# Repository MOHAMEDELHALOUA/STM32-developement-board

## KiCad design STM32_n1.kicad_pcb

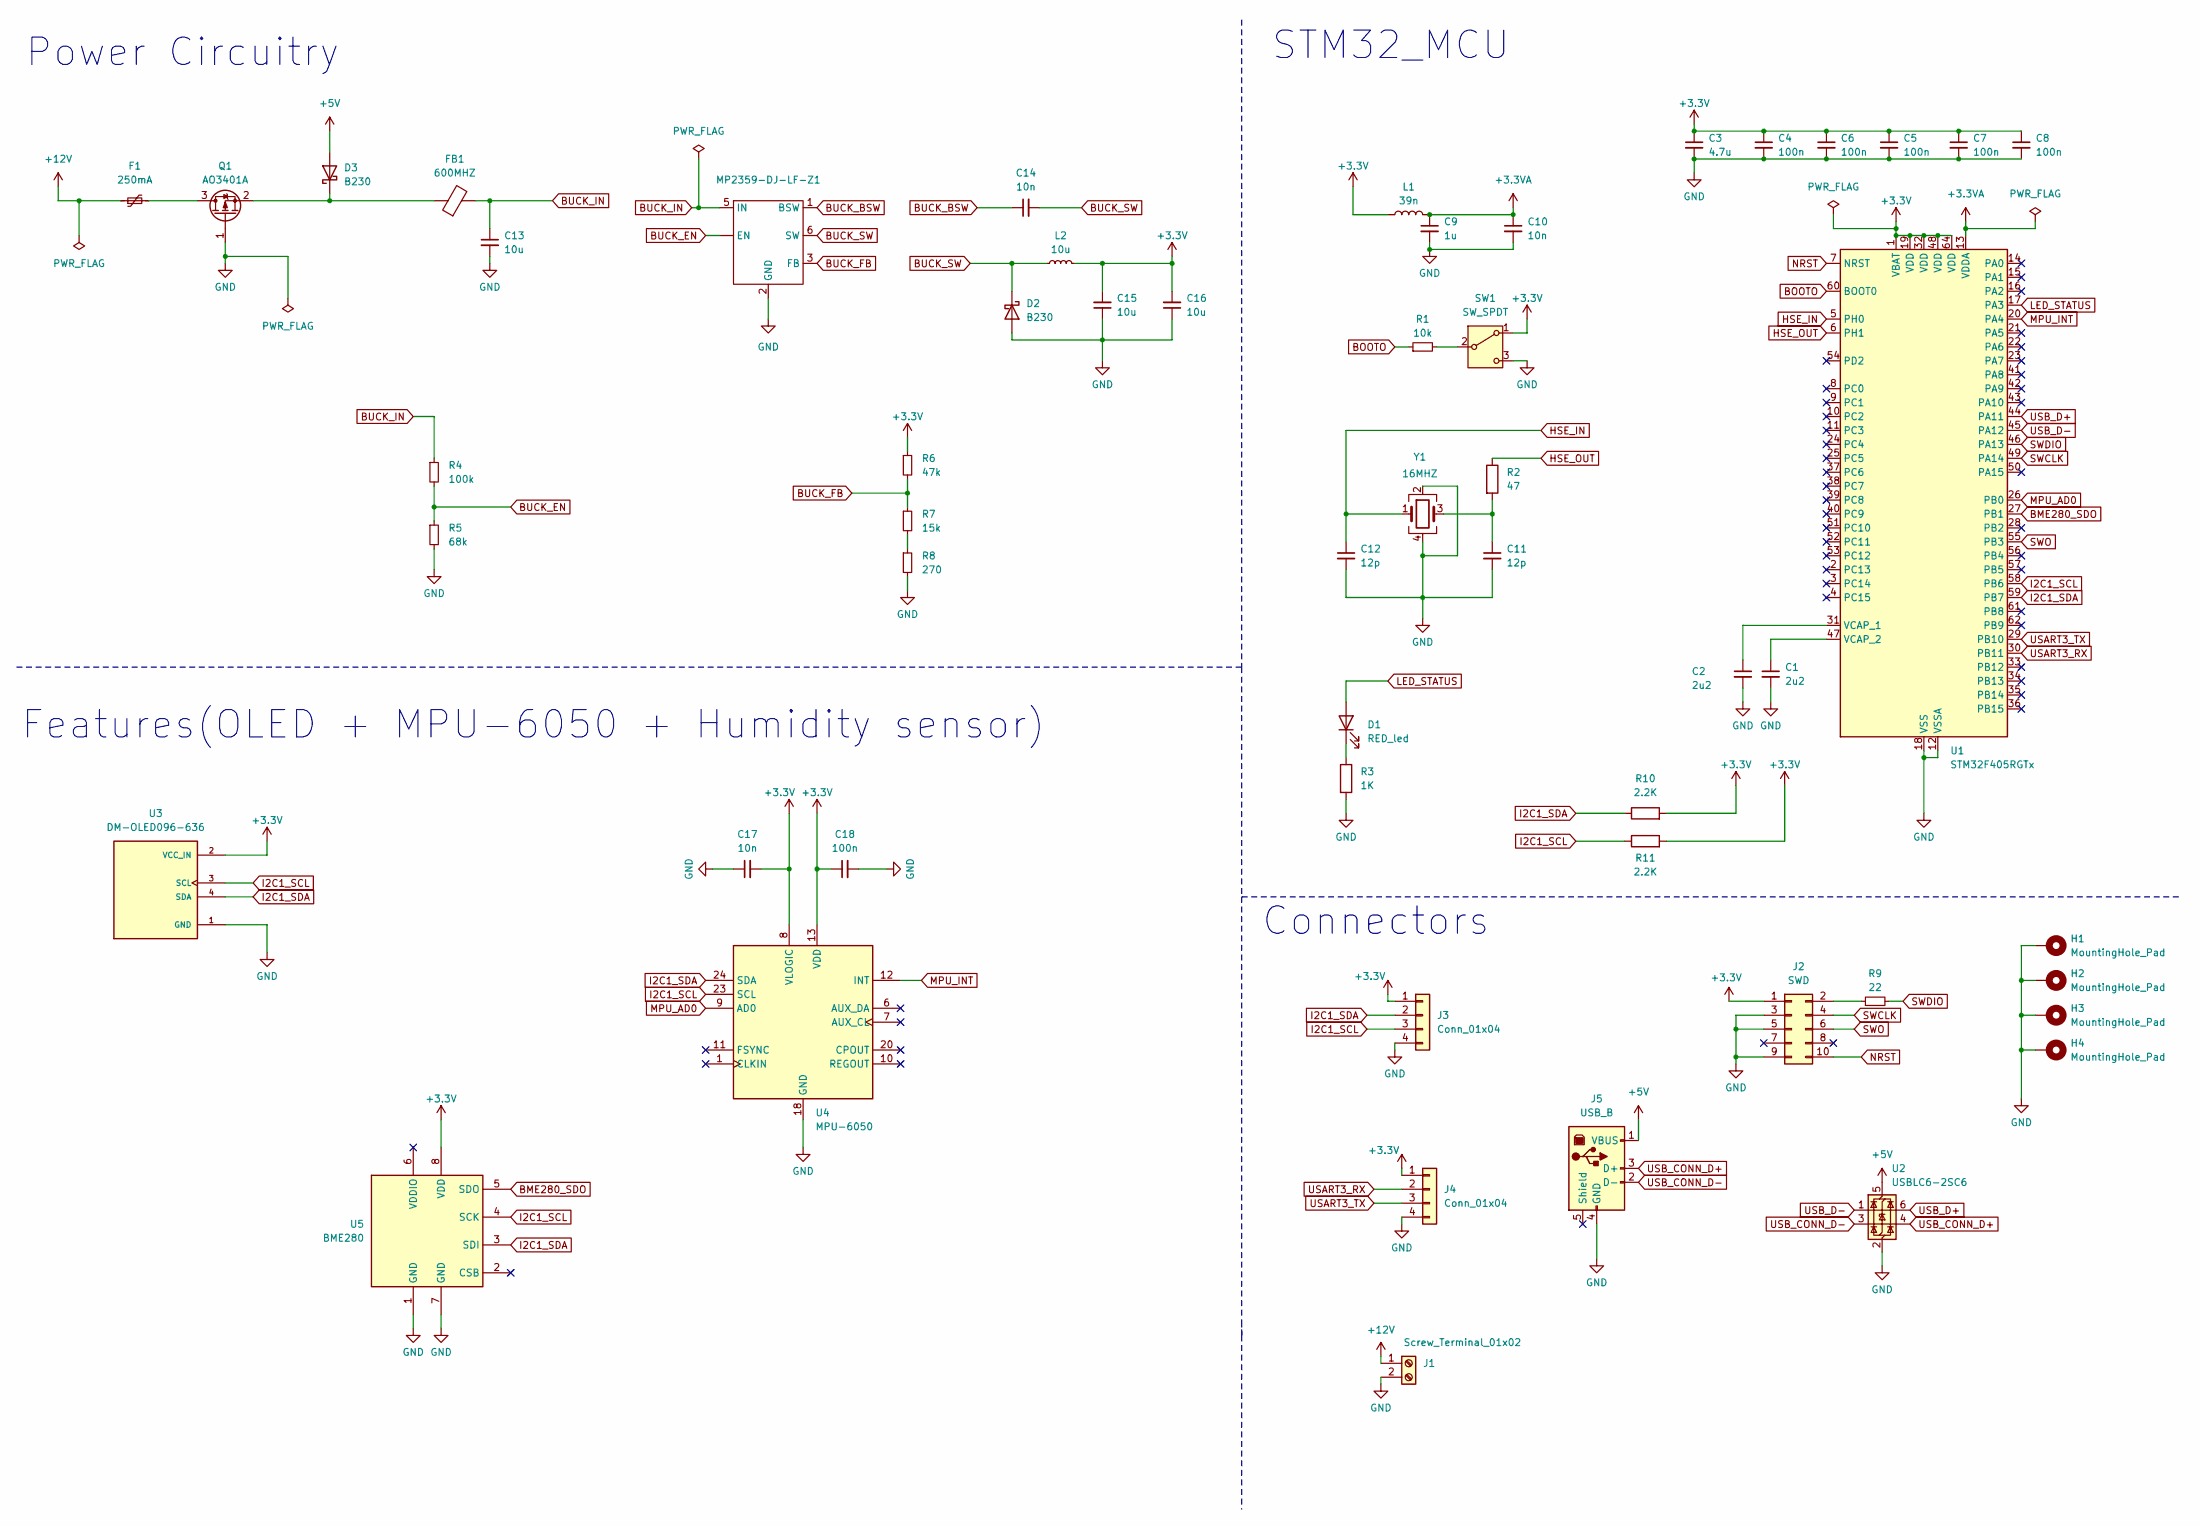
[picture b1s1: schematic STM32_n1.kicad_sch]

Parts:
C1, C2: 2u2; C_0603_1608Metric
C3: 4.7u; C_0603_1608Metric
C4, C5, C6, C7, C8, C18: 100n; C_0402_1005Metric
C9: 1u; C_0402_1005Metric
C10, C14, C17: 10n; C_0402_1005Metric
C11, C12: 12p; C_0402_1005Metric
C13, C15, C16: 10u; C_1206_3216Metric
D1: RED_led; LED_0201_0603Metric
D2, D3: B230; D_SMB
F1: 250mA; Fuse_1206_3216Metric
FB1: 600MHZ; L_0805_2012Metric
H1, H2, H3, H4: MountingHole_Pad; MountingHole_3mm_Pad_Via
J1: Screw_Terminal_01x02; TerminalBlock_Phoenix_PT-1,5-2-3.5-H_1x02_P3.50mm_Horizontal
J2: SWD; PinHeader_2x05_P2.54mm_Vertical_SMD
J3, J4: Conn_01x04; Molex_PicoBlade_53048-0410_1x04_P1.25mm_Horizontal
J5: USB_B; HRS_ZX62D-B-5P8
L1: 39n; L_Sunlord_MWSA0402S
L2: 10u; L_Sunlord_MWSA0518S
MP2359-DJ-LF-Z1: SOT-23-6
Q1: AO3401A; SOT-23
R1: 10k; R_0402_1005Metric
R2: 47; R_0402_1005Metric
R3: 1K; R_0603_1608Metric
R4: 100k; R_0201_0603Metric
R5: 68k; R_0201_0603Metric
R6: 47k; R_0201_0603Metric
R7: 15k; R_0201_0603Metric
R8: 270; R_0201_0603Metric
R9: 22; R_0402_1005Metric
R10, R11: 2.2K; R_0402_1005Metric
SW1: SW_SPDT; SW_SPDT_PCM12
U1: STM32F405RGTx; LQFP-64_10x10mm_P0.5mm
U2: USBLC6-2SC6; SOT-23-6
U3: DM-OLED096-636; MODULE_DM-OLED096-636; PARTREV 2018-09-10
U4: MPU-6050; QFN50P400X400X95-24N
U5: BME280; Bosch_LGA-8_2.5x2.5mm_P0.65mm_ClockwisePinNumbering
Y1: 16MHZ; Crystal_SMD_3225-4Pin_3.2x2.5mm

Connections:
+3.3V: C3.1, C4.1, C5.1, C6.1, C7.1, C8.1, C15.2, C16.2, C17.2, C18.1, J2.1, J3.1, J4.1, L1.1, L2.2, R6.1, R10.2, R11.2, SW1.1 (A), U1.1 (VBAT), U1.19 (VDD), U1.32 (VDD), U1.48 (VDD), U1.64 (VDD), U3.2 (VCC_IN), U4.8 (VLOGIC), U4.13 (VDD), U5.8 (VDD)
+3.3VA: C9.1, C10.1, L1.2, U1.13 (VDDA)
+5V: D3.2 (A), J5.1 (VBUS), U2.5 (VBUS)
+12V: F1.1, J1.1
BME280_SDO: U1.27 (PB1), U5.5 (SDO)
BOOTO: R1.1, U1.60 (BOOT0)
BUCK_BSW: C14.1, MP2359-DJ-LF-Z1.1 (BSW)
BUCK_EN: MP2359-DJ-LF-Z1. (EN), R4.2, R5.1
BUCK_FB: MP2359-DJ-LF-Z1.3 (FB), R6.2, R7.1
BUCK_IN: C13.1, FB1.2, MP2359-DJ-LF-Z1.5 (IN), R4.1
BUCK_SW: C14.2, D2.1 (K), L2.1, MP2359-DJ-LF-Z1.6 (SW)
GND: C1.2, C2.2, C3.2, C4.2, C5.2, C6.2, C7.2, C8.2, C9.2, C10.2, C11.2, C12.2, C13.2, C15.1, C16.1, C17.1, C18.2, D2.2 (A), H1.1, H2.1, H3.1, H4.1, J1.2, J2.3, J2.5, J2.9, J3.4, J4.4, J5.4 (GND), MP2359-DJ-LF-Z1.2 (GND), Q1.1 (G), R3.2, R5.2, R8.2, SW1.3 (C), U1.12 (VSSA), U1.18 (VSS), U1.63 (VSS), U2.2 (GND), U3.1 (GND), U4.18 (GND), U5.1 (GND), U5.7 (GND), Y1.2, Y1.4
HSE_IN: C12.1, U1.5 (PH0), Y1.1
HSE_OUT: R2.1, U1.6 (PH1)
I2C1_SCL: J3.3, R11.1, U1.58 (PB6), U3.3 (SCL), U4.23 (SCL), U5.4 (SCK)
I2C1_SDA: J3.2, R10.1, U1.59 (PB7), U3.4 (SDA), U4.24 (SDA), U5.3 (SDI)
LED_STATUS: D1.2 (A), U1.17 (PA3)
MPU_AD0: U1.26 (PB0), U4.9 (AD0)
MPU_INT: U1.20 (PA4), U4.12 (INT)
NRST: J2.10, U1.7 (NRST)
unnamed: C11.1, R2.2, Y1.3
unnamed: D1.1 (K), R3.1
unnamed: D3.1 (K), FB1.1, Q1.2 (S)
unnamed: J2.2, R9.1
unnamed: F1.2, Q1.3 (D)
unnamed: R7.2, R8.1
unnamed: R1.2, SW1.2 (B)
unnamed: C2.1, U1.31 (VCAP_1)
unnamed: C1.1, U1.47 (VCAP_2)
SWCLK: J2.4, U1.49 (PA14)
SWDIO: R9.2, U1.46 (PA13)
SWO: J2.6, U1.55 (PB3)
USART3_RX: J4.2, U1.30 (PB11)
USART3_TX: J4.3, U1.29 (PB10)
USB_CONN_D+: J5.3 (D+), U2.4 (I/O2)
USB_CONN_D-: J5.2 (D-), U2.3 (I/O2)
USB_D+: U1.44 (PA11), U2.6 (I/O1)
USB_D-: U1.45 (PA12), U2.1 (I/O1)

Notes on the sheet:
STM32_MCU
Connectors
Power Circuitry
Features(OLED + MPU-6050 + Humidity sensor)

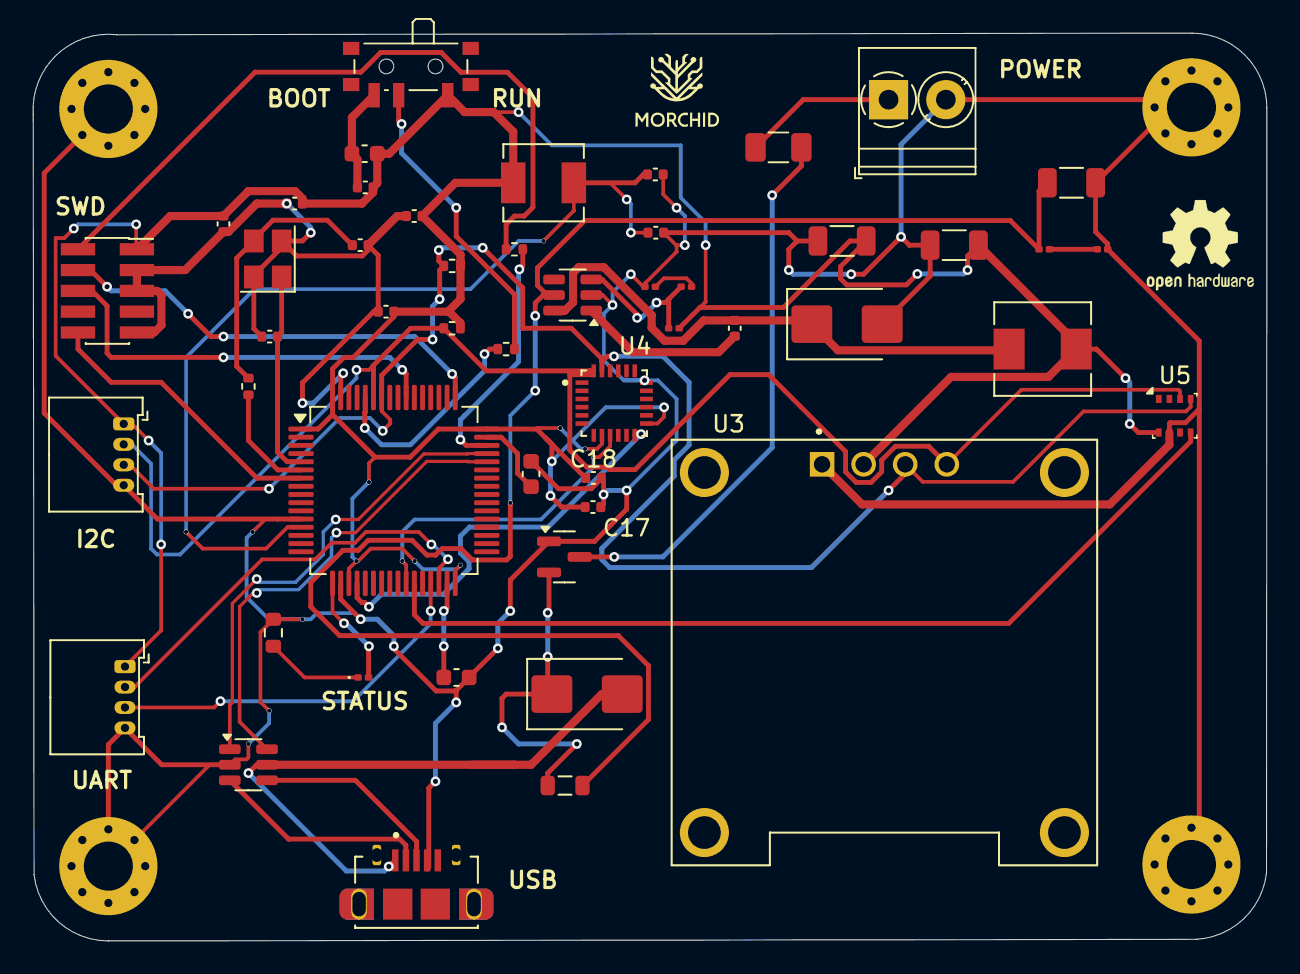
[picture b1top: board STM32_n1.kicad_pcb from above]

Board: 4 copper layers, 75.4 x 55.5 mm, 54 parts (0 on the bottom side), 38 nets.

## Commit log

2025-01-13 This is my recent desing of a PCB developement board based on the STM32 MCU
2025-07-26 Added Twizy_V2X_Board.drawio
